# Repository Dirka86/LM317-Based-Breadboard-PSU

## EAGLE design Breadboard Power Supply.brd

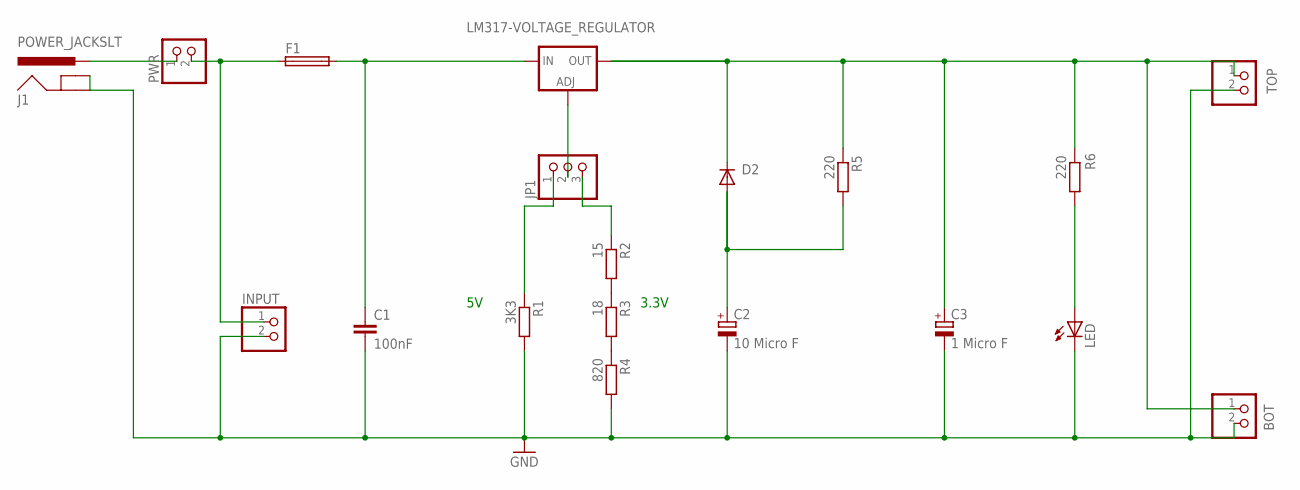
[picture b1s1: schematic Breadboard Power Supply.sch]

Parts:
BOT: PINHD-1X2; 1X02
C1: 100nF; C025-030X050
C2: 10 Micro F; E2-5
C3: 1 Micro F; E2-5
D2: 1N4004; DO41-10
F1: SH22,5A
INPUT: PINHD-1X2; 1X02
J1: POWER_JACKSLT; POWER_JACK_SLOT
JP1: PINHD-1X3; 1X03
LED: TLLR4400; LED3MM
LM317-VOLTAGE_REGULATOR: LM138-TS; TO220S
PWR: PINHD-1X2; 1X02
R1: 3K3; 0207/12
R2: 15; 0207/12
R3: 18; 0207/12
R4: 820; 0207/12
R5, R6: 220; 0207/12
TOP: PINHD-1X2; 1X02

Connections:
GND: BOT.2, C1.2, C2.-, C3.-, INPUT.2, J1.GND@1 (GNDBREAK), J1.GND@2 (GND), LED.K (C), R1.2, R4.2, TOP.2
unnamed: R2.2, R3.1
unnamed: R3.2, R4.1
unnamed: JP1.3, R2.1
unnamed: JP1.1, R1.1
unnamed: JP1.2, LM317-VOLTAGE_REGULATOR.1 (ADJ)
unnamed: C1.1, F1.2, LM317-VOLTAGE_REGULATOR.3 (IN)
unnamed: BOT.1, C3.+, D2.C, LM317-VOLTAGE_REGULATOR.2 (OUT), R5.1, R6.1, TOP.1
unnamed: C2.+, D2.A, R5.2
unnamed: J1.PWR, PWR.1
unnamed: LED.A, R6.2
VIN: F1.1, INPUT.1, PWR.2

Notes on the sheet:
3.3V

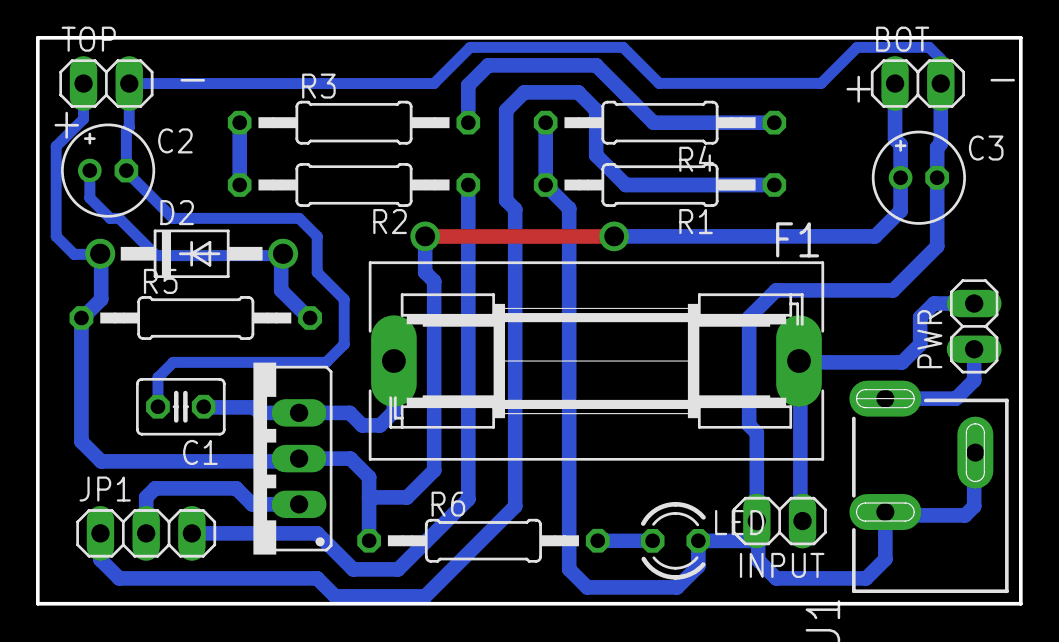
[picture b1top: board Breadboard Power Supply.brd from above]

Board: 2 copper layers, 54.6 x 31.4 mm, 19 parts (0 on the bottom side), 12 nets.

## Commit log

2014-08-03 :tada: Added .gitattributes & .gitignore files
2014-08-03 Breadboard PSU
    Just a little Breadboard PSU that I've built around the LM317. It is
    working nicely so if you need to drive any low 3.3V module then you can
    make use of this.
